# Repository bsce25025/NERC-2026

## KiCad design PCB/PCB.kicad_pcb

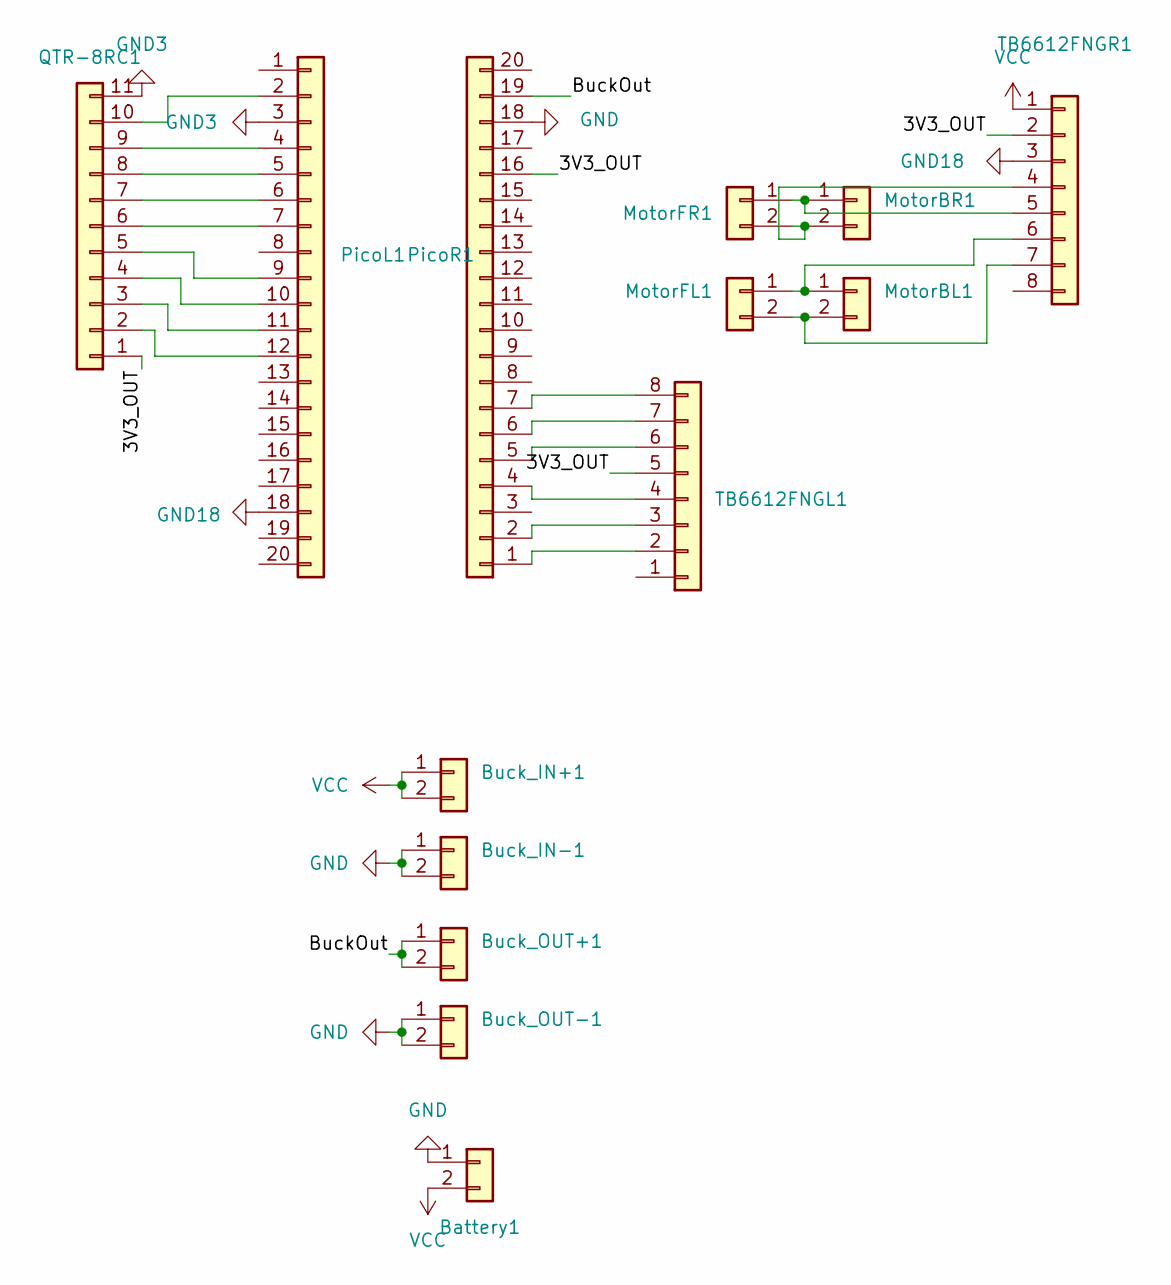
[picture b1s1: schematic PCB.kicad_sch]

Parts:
Battery1: Conn_01x02; TerminalBlock_Phoenix_MKDS-1,5-2-5.08_1x02_P5.08mm_Horizont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
Buck_IN+1: Conn_01x02; PinHeader_1x02_P2.54mm_Vertical
Buck_IN-1: Conn_01x02; PinHeader_1x02_P2.54mm_Vertical
Buck_OUT+1: Conn_01x02; PinHeader_1x02_P2.54mm_Vertical
Buck_OUT-1: Conn_01x02; PinHeader_1x02_P2.54mm_Vertical
MotorBL1: Conn_01x02; TerminalBlock_Phoenix_MKDS-1,5-2-5.08_1x02_P5.08mm_Horizont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
MotorBR1: Conn_01x02; TerminalBlock_Phoenix_MKDS-1,5-2-5.08_1x02_P5.08mm_Horizont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
MotorFL1: Conn_01x02; TerminalBlock_Phoenix_MKDS-1,5-2-5.08_1x02_P5.08mm_Horizont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
MotorFR1: Conn_01x02; TerminalBlock_Phoenix_MKDS-1,5-2-5.08_1x02_P5.08mm_Horizont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
PicoL1: Conn_01x20; PinHeader_1x20_P2.54mm_Vertical
PicoR1: Conn_01x20; PinHeader_1x20_P2.54mm_Vertical
QTR-8RC1: Conn_01x11; PinHeader_1x11_P2.54mm_Vertical
TB6612FNGL1, TB6612FNGR1: Conn_01x08; PinHeader_1x08_P2.54mm_Vertical

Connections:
/3V3_OUT: PicoR1.16, QTR-8RC1.1, TB6612FNGL1.5, TB6612FNGR1.2
/BuckOut: Buck_OUT+1.1, Buck_OUT+1.2, PicoR1.19
GND: Battery1.1, Buck_IN-1.1, Buck_IN-1.2, Buck_OUT-1.1, Buck_OUT-1.2, PicoR1.18
GND3: PicoL1.3, QTR-8RC1.11
GND18: PicoL1.18, TB6612FNGR1.3
unnamed: MotorBL1.1, MotorFL1.1, TB6612FNGR1.6
unnamed: MotorBL1.2, MotorFL1.2, TB6612FNGR1.7
unnamed: MotorBR1.1, MotorFR1.1, TB6612FNGR1.5
unnamed: MotorBR1.2, MotorFR1.2, TB6612FNGR1.4
unnamed: PicoL1.2, QTR-8RC1.10
unnamed: PicoL1.4, QTR-8RC1.9
unnamed: PicoL1.5, QTR-8RC1.8
unnamed: PicoL1.6, QTR-8RC1.7
unnamed: PicoL1.7, QTR-8RC1.6
unnamed: PicoL1.9, QTR-8RC1.5
unnamed: PicoL1.10, QTR-8RC1.4
unnamed: PicoL1.11, QTR-8RC1.3
unnamed: PicoL1.12, QTR-8RC1.2
unnamed: PicoR1.1, TB6612FNGL1.2
unnamed: PicoR1.2, TB6612FNGL1.3
unnamed: PicoR1.4, TB6612FNGL1.4
unnamed: PicoR1.5, TB6612FNGL1.6
unnamed: PicoR1.6, TB6612FNGL1.7
unnamed: PicoR1.7, TB6612FNGL1.8
VCC: Battery1.2, Buck_IN+1.1, Buck_IN+1.2, TB6612FNGR1.1

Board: 2 copper layers, 14 parts (4 on the bottom side), 25 nets, no tracks yet.

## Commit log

2026-01-21 PCB design
2026-01-22 v1
    1st completed version of PCB
    Size is large than needed
2026-01-22 moved to folder for merging later
2026-01-22 resized and gerber
2026-01-22 placed gerber files in a folder
2026-01-22 page setup and pdf generation
2026-01-22 centralized
2026-01-22 auto
2026-01-23 100x100
2026-01-23 75x75 and names
2026-01-23 screw holes
2026-01-26 sensor array
2026-01-26 pin deffinations
2026-01-26 sensors
2026-01-26 PID and Navigation
2026-01-26 motors
2026-01-26 Main Code File
    Main.cpp for this code
2026-01-27 16 sensor
2026-02-05 100x100 pdf
2026-02-05 75x75
2026-02-06 GitHub
2026-02-13 Add PCB 100x100 1.0mm single-sided PDF
    Add PCB/PDF/PCB 100x100 1.0mm single sided unmirrored.pdf — a new PDF containing 100x100mm, 1.0mm-thickness single-sided (unmirrored) PCB artwork.
2026-02-15 Turns
2026-02-15 cleanup
2026-02-15 QTR-8A
